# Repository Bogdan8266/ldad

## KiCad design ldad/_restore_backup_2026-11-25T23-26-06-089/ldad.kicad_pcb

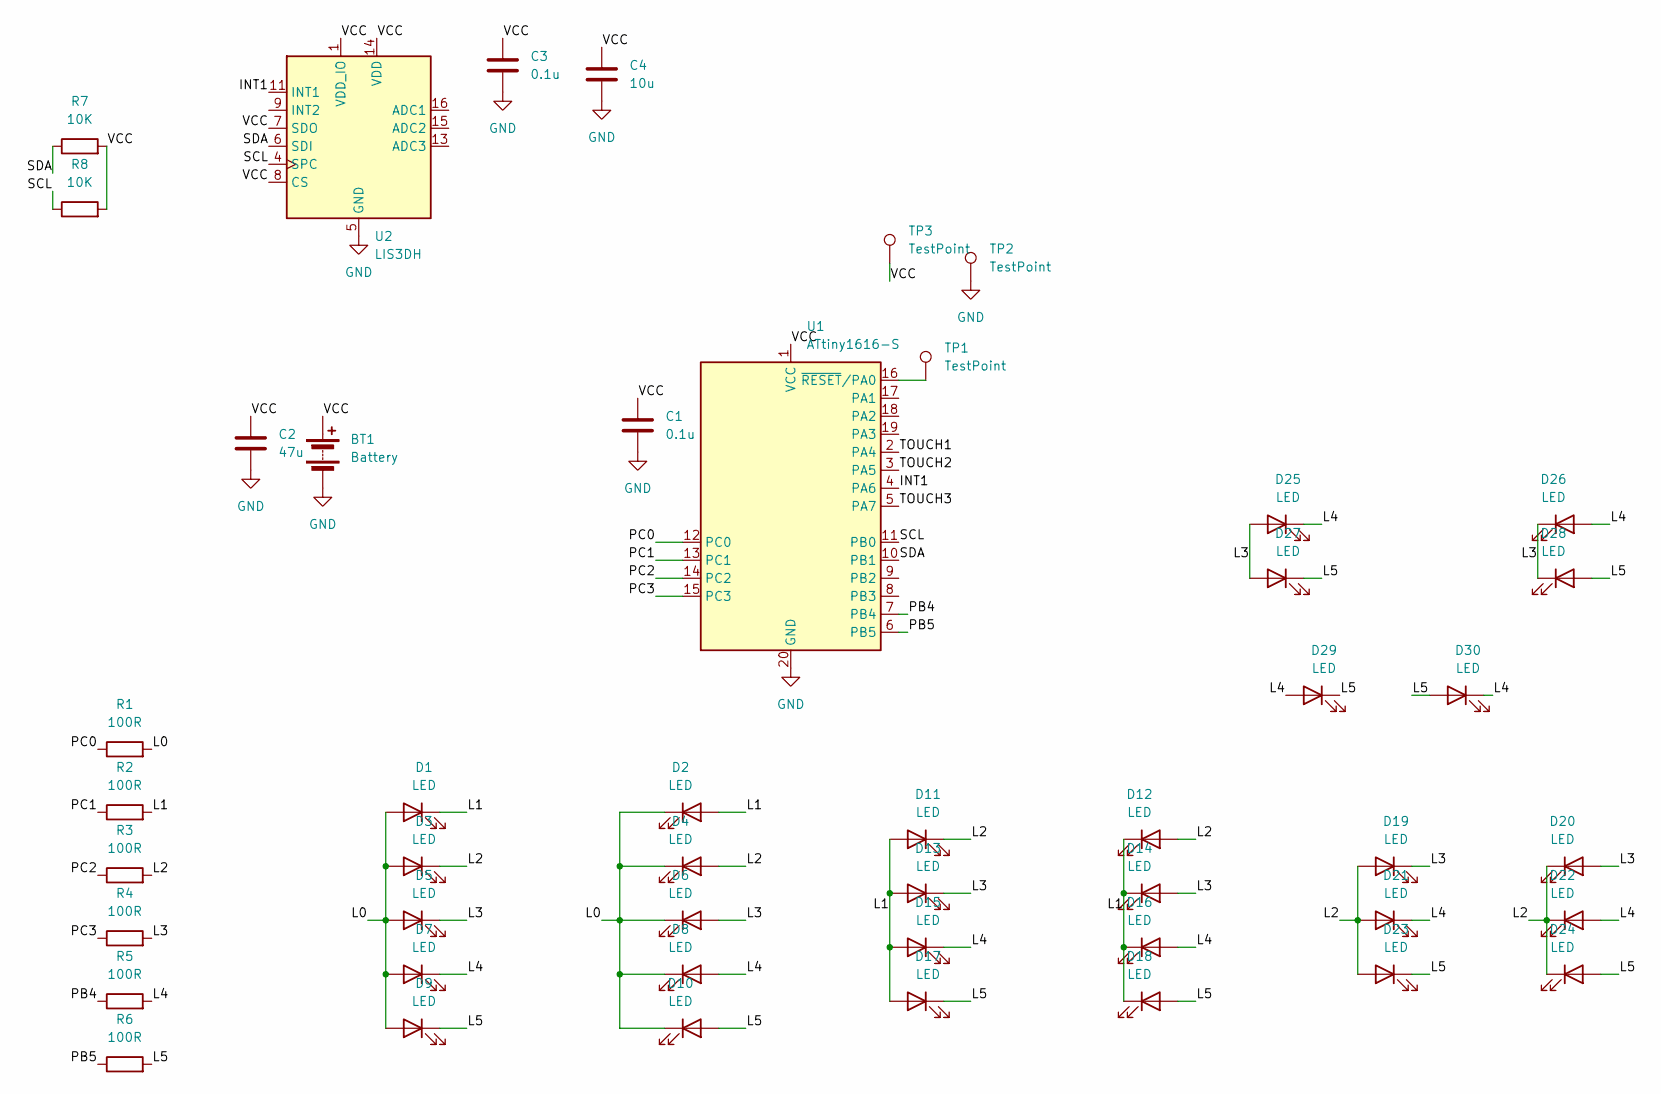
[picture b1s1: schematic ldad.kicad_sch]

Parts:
BT1: Battery; BatteryHolder_Multicomp_BC-2001_1x2032
C1, C3: 0.1u; C_0805_2012Metric_Pad1.18x1.45mm_HandSolder
C2: 47u; C_0805_2012Metric_Pad1.18x1.45mm_HandSolder
C4: 10u; C_0805_2012Metric_Pad1.18x1.45mm_HandSolder
D1, D2, D3, D4, D5, D6, D7, D8, D9, D10, D11, D12, D13, D14, D15, D16, D17, D18, D19, D20, D21, D22, D23, D24, D25, D26, D27, D28, D29, D30: LED; LED_0603_1608Metric_Pad1.05x0.95mm_HandSolder
R1, R2, R3, R4, R5, R6: 100R; R_0805_2012Metric_Pad1.20x1.40mm_HandSolder
R7, R8: 10K; R_0805_2012Metric_Pad1.20x1.40mm_HandSolder
TP1, TP2, TP3: TestPoint; TestPoint_Pad_D1.5mm
U1: ATtiny1616-S; SOIC-20W_7.5x12.8mm_P1.27mm
U2: LIS3DH; LGA-16_3x3mm_P0.5mm_LayoutBorder3x5y

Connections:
/INT1: U1.4 (PA6), U2.11 (INT1)
/L0: D1.2 (A), D2.1 (K), D3.2 (A), D4.1 (K), D5.2 (A), D6.1 (K), D7.2 (A), D8.1 (K), D9.2 (A), D10.1 (K), R1.2
/L1: D1.1 (K), D2.2 (A), D11.2 (A), D12.1 (K), D13.2 (A), D14.1 (K), D15.2 (A), D16.1 (K), D17.2 (A), D18.1 (K), R2.2
/L2: D3.1 (K), D4.2 (A), D11.1 (K), D12.2 (A), D19.2 (A), D20.1 (K), D21.2 (A), D22.1 (K), D23.2 (A), D24.1 (K), R3.2
/L3: D5.1 (K), D6.2 (A), D13.1 (K), D14.2 (A), D19.1 (K), D20.2 (A), D25.2 (A), D26.1 (K), D27.2 (A), D28.1 (K), R4.2
/L4: D7.1 (K), D8.2 (A), D15.1 (K), D16.2 (A), D21.1 (K), D22.2 (A), D25.1 (K), D26.2 (A), D29.2 (A), D30.1 (K), R5.2
/L5: D9.1 (K), D10.2 (A), D17.1 (K), D18.2 (A), D23.1 (K), D24.2 (A), D27.1 (K), D28.2 (A), D29.1 (K), D30.2 (A), R6.2
/PB4: R5.1, U1.7 (PB4)
/PB5: R6.1, U1.6 (PB5)
/PC0: R1.1, U1.12 (PC0)
/PC1: R2.1, U1.13 (PC1)
/PC2: R3.1, U1.14 (PC2)
/PC3: R4.1, U1.15 (PC3)
/SCL: R8.1, U1.11 (PB0), U2.4 (SPC)
/SDA: R7.1, U1.10 (PB1), U2.6 (SDI)
/TOUCH1: U1.2 (PA4)
/TOUCH2: U1.3 (PA5)
/TOUCH3: U1.5 (PA7)
/VCC: BT1.1 (+), C1.1, C2.1, C3.1, C4.1, R7.2, R8.2, TP3.1 (1_1), U1.1 (VCC), U2.1 (VDD_IO), U2.7 (SDO), U2.8 (CS), U2.14 (VDD)
GND: BT1.2 (-), C1.2, C2.2, C3.2, C4.2, TP2.1 (1_1), U1.20 (GND), U2.5 (GND), U2.10 (GND), U2.12 (GND)
unnamed: TP1.1 (1_1), U1.16 (~RESET/PA0)

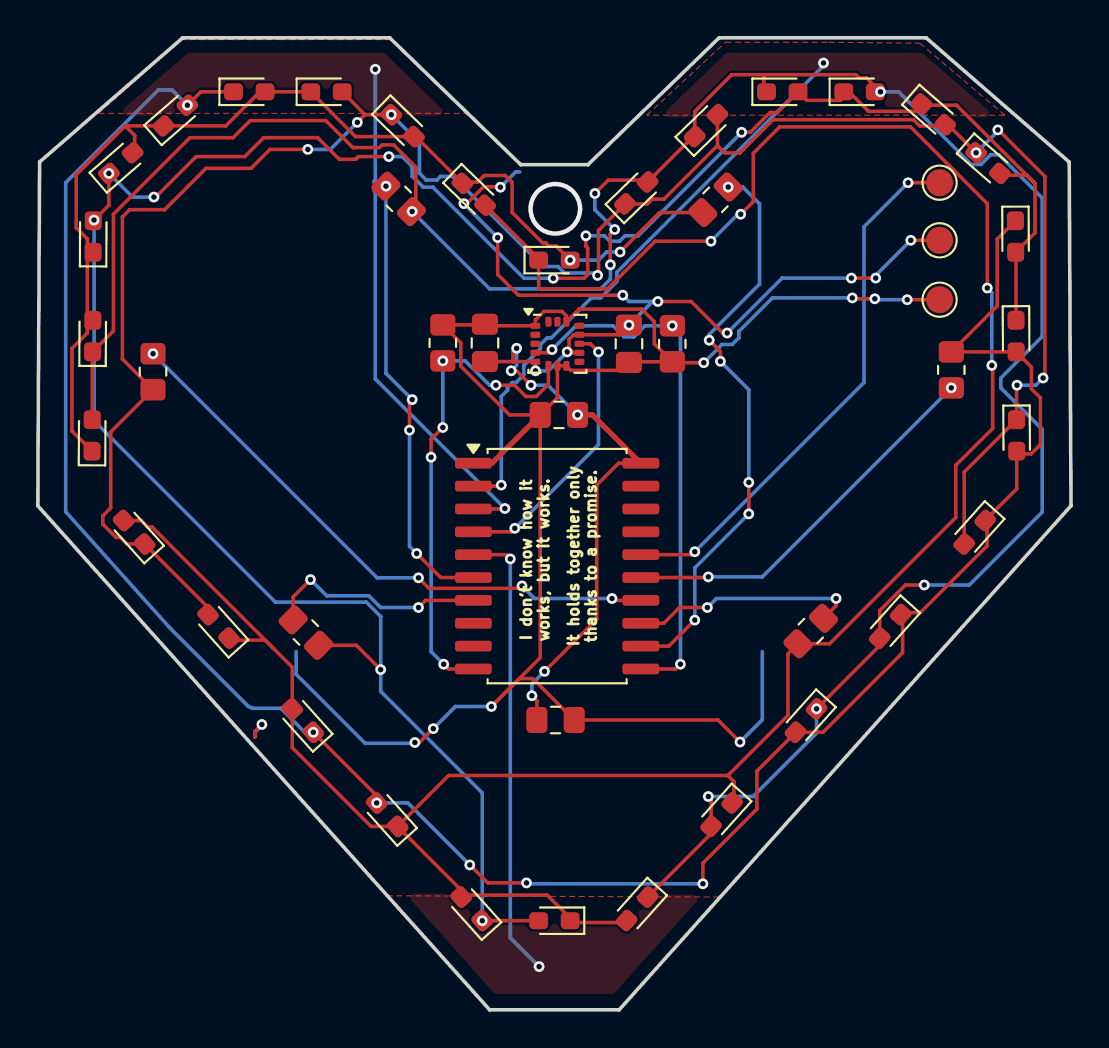
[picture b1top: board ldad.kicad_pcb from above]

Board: 2 copper layers, 57.4 x 54.0 mm, 48 parts (1 on the bottom side), 18 nets.
